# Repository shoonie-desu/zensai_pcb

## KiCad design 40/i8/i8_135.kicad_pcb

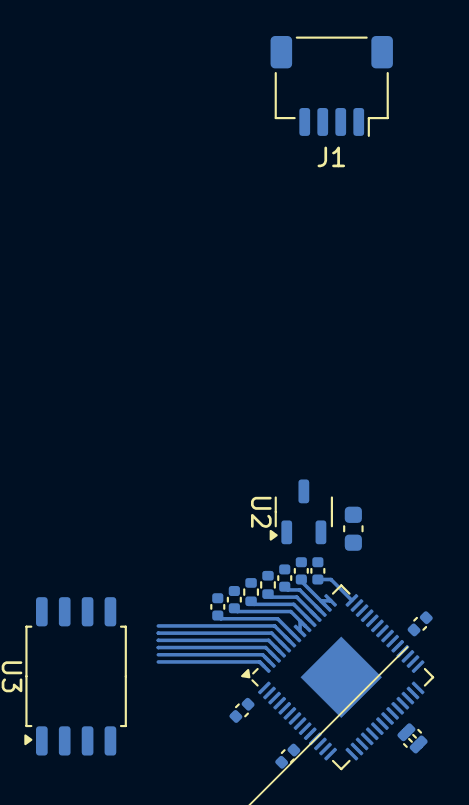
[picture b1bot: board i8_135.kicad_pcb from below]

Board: 2 copper layers, 17 parts (17 on the bottom side), 14 nets.

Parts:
C1, C5: 1u; C_0402_1005Metric
C2, C3, C6, C7, C8, C9, C10, C11: 100n; C_0402_1005Metric
C4: 10u; C_0603_1608Metric
J1: ZX-SH1.0-4PWT; JST_SH_SM04B-SRSS-TB_1x04-1MP_P1.00mm_Horizontal
R1, R2: 27; R_0402_1005Metric
U1: RP2040; QFN-56-1EP_7x7mm_P0.4mm_EP3.2x3.2mm
U2: XC6206P332MR-G; SOT-23-3
U3: W25Q128JVS; SOIC-8_5.3x5.3mm_P1.27mm

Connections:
+1V1: C1.1, C2.1, C3.1, U1.23 (DVDD), U1.45 (VREG_VOUT), U1.50 (DVDD)
+3V3: C4.1, C5.1, C6.1, C7.1, C8.1, C9.1, C10.1, C11.1, U1.1 (IOVDD), U1.10 (IOVDD), U1.22 (IOVDD), U1.33 (IOVDD), U1.42 (IOVDD), U1.43 (ADC_AVDD), U1.44 (VREG_IN), U1.48 (USB_VDD), U1.49 (IOVDD), U2.2 (VO), U3.8 (VCC)
+5V: J1.1, U2.3 (VI)
D+: J1.3, R1.1
D-: J1.2, R2.2
GND: C1.2, C2.2, C3.2, C4.2, C5.2, C6.2, C7.2, C8.2, C9.2, C10.2, C11.2, J1.4, U1.19 (TESTEN), U1.57 (GND), U2.1 (GND), U3.4 (GND)
unnamed: R2.1, U1.46 (USB_DM)
unnamed: R1.2, U1.47 (USB_DP)
Q_CLK: U1.52 (QSPI_SCLK), U3.6 (CLK)
Q_IO0: U1.53 (QSPI_SD0), U3.5 (DI/IO_{0})
Q_IO1: U1.55 (QSPI_SD1), U3.2 (DO/IO_{1})
Q_IO2: U1.54 (QSPI_SD2), U3.3 (~WP/IO_{2})
Q_IO3: U1.51 (QSPI_SD3), U3.7 (~HOLD/~RESET/IO_{3})
Q_SEL: U1.56 (QSPI_SS), U3.1 (~CS)

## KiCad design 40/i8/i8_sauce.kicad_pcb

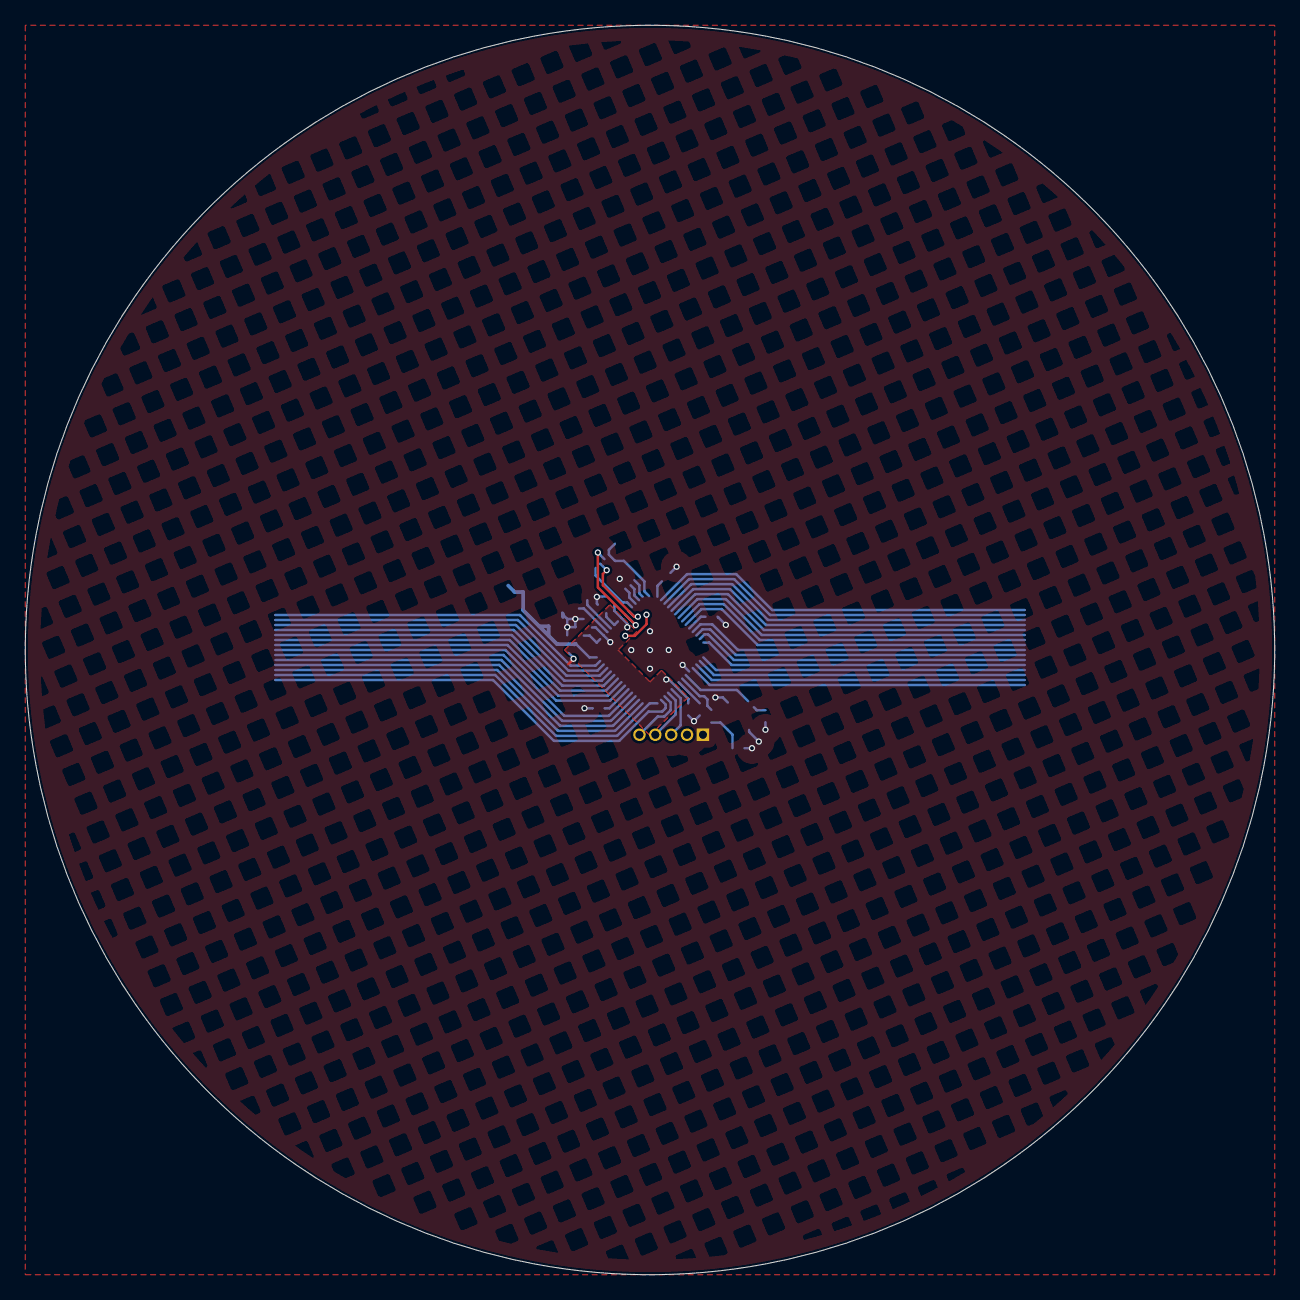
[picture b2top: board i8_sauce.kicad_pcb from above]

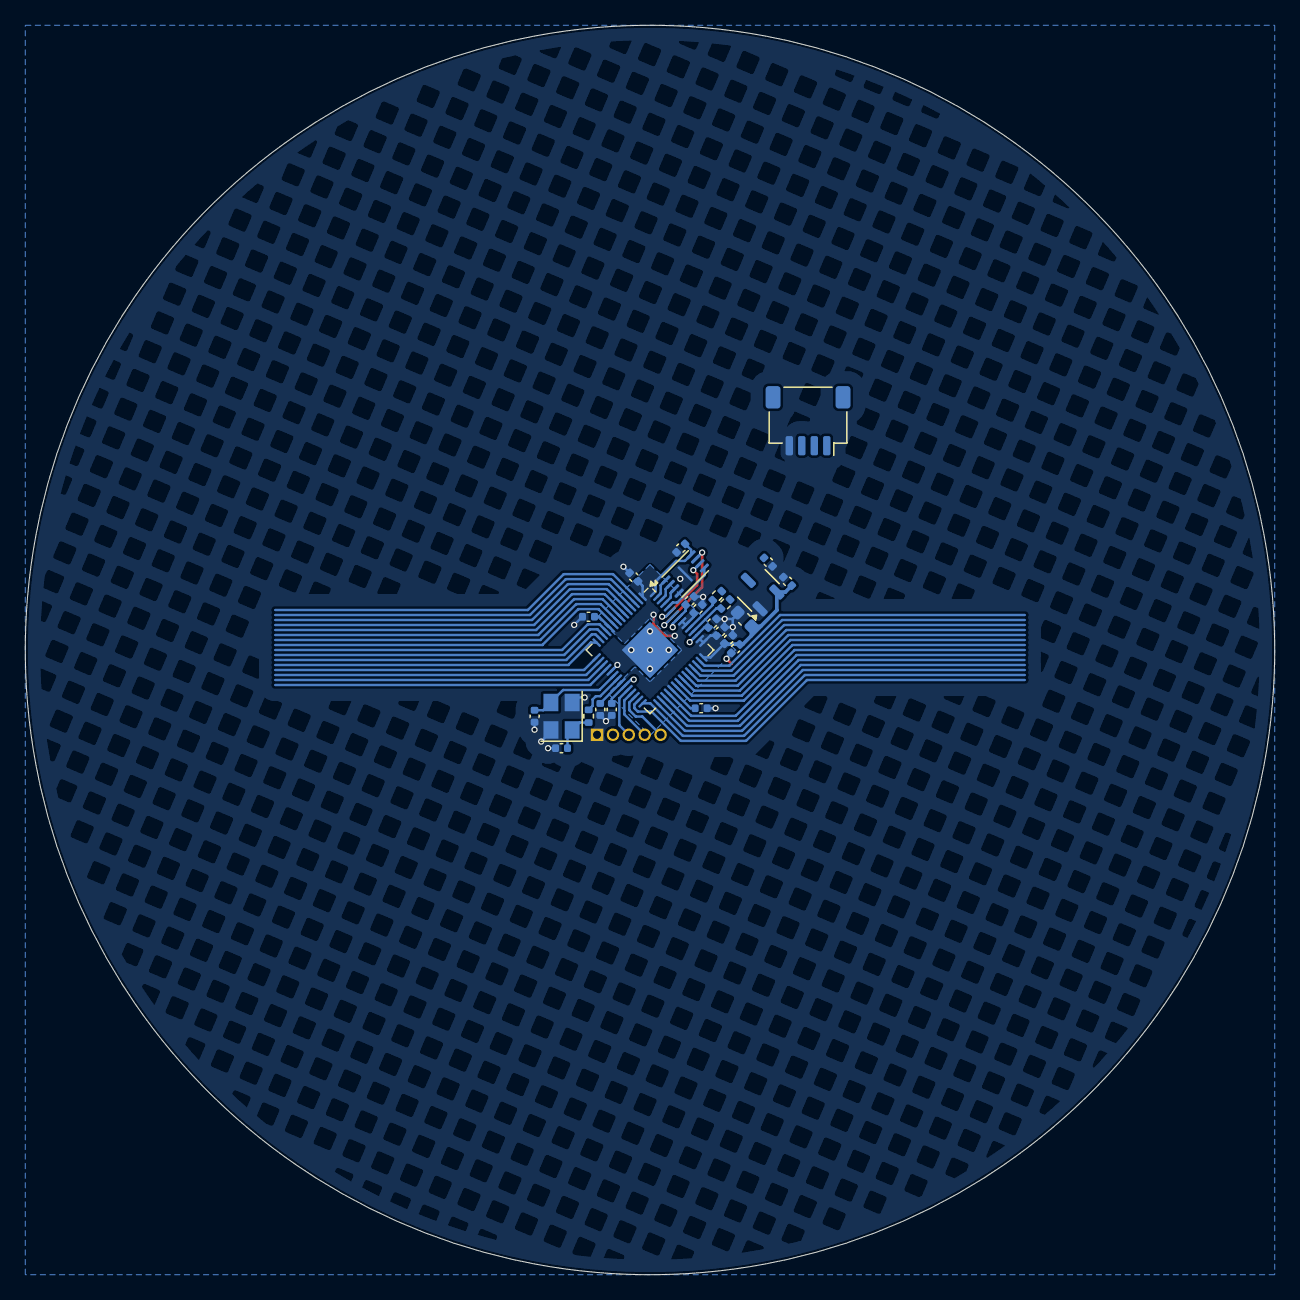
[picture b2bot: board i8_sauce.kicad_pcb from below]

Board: 2 copper layers, 100.0 x 100.0 mm, 26 parts (25 on the bottom side), 20 nets.

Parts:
C1, C5, C13, C14, C15: 1u; C_0402_1005Metric
C2, C3, C6, C7, C8, C9, C10, C11, C12: 100n; C_0402_1005Metric
C4: 10u; C_0603_1608Metric
C16, C17: 22p; C_0402_1005Metric
J1: ZX-SH1.0-4PWT; JST_SH_SM04B-SRSS-TB_1x04-1MP_P1.00mm_Horizontal
J2: Conn_DEBUG; PinHeader_1x05_P1.27mm_Vertical
R1, R2: 27; R_0402_1005Metric
R4: 1k; R_0402_1005Metric
U1: XC6206P332MR-G; SOT-23-3
U2: RP2040; QFN-56-1EP_7x7mm_P0.4mm_EP3.2x3.2mm
U3: W25Q16JVUXIQ; Winbond_USON-8-1EP_3x2mm_P0.5mm_EP0.2x1.6mm
Y1: Crystal_GND24; Crystal_SMD_3225-4Pin_3.2x2.5mm

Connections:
+1V1: C1.1, C2.1, C3.1, U2.23 (DVDD), U2.45 (VREG_VOUT), U2.50 (DVDD)
+3V3: C4.1, C5.1, C6.1, C7.1, C8.1, C9.1, C10.1, C11.1, C12.1, C14.1, C15.2, J2.2, U1.2 (VO), U2.1 (IOVDD), U2.10 (IOVDD), U2.22 (IOVDD), U2.33 (IOVDD), U2.42 (IOVDD), U2.43 (ADC_AVDD), U2.44 (VREG_IN), U2.48 (USB_VDD), U2.49 (IOVDD), U3.8 (VCC)
+5V: C13.1, J1.1, U1.3 (VI)
D+: J1.3, R1.1
D-: J1.2, R2.2
GND: C1.2, C2.2, C3.2, C4.2, C5.2, C6.2, C7.2, C8.2, C9.2, C10.2, C11.2, C12.2, C13.2, C14.2, C15.1, C16.1, C17.1, J1.4, J2.1, U1.1 (GND), U2.19 (TESTEN), U2.57 (GND), U3.4 (GND), U3.9 (EP), Y1.2, Y1.4
unnamed: C17.2, R4.2, Y1.1
unnamed: R2.1, U2.46 (USB_DM)
unnamed: R1.2, U2.47 (USB_DP)
Q_CLK: U2.52 (QSPI_SCLK), U3.6 (CLK)
Q_IO0: U2.53 (QSPI_SD0), U3.5 (DI/IO_{0})
Q_IO1: U2.55 (QSPI_SD1), U3.2 (DO/IO_{1})
Q_IO2: U2.54 (QSPI_SD2), U3.3 (~WP/IO_{2})
Q_IO3: U2.51 (QSPI_SD3), U3.7 (~HOLD/~RESET/IO_{3})
Q_SEL: U2.56 (QSPI_SS), U3.1 (~CS)
RST: J2.5, U2.26 (RUN)
SWC: J2.3, U2.24 (SWCLK)
SWD: J2.4, U2.25 (SWD)
XIN: C16.2, U2.20 (XIN), Y1.3
XOUT: R4.1, U2.21 (XOUT)

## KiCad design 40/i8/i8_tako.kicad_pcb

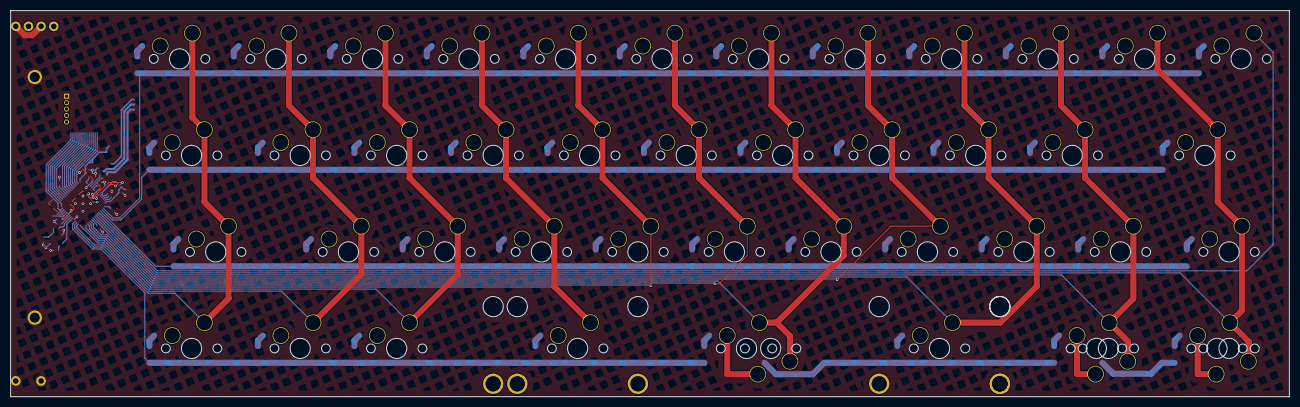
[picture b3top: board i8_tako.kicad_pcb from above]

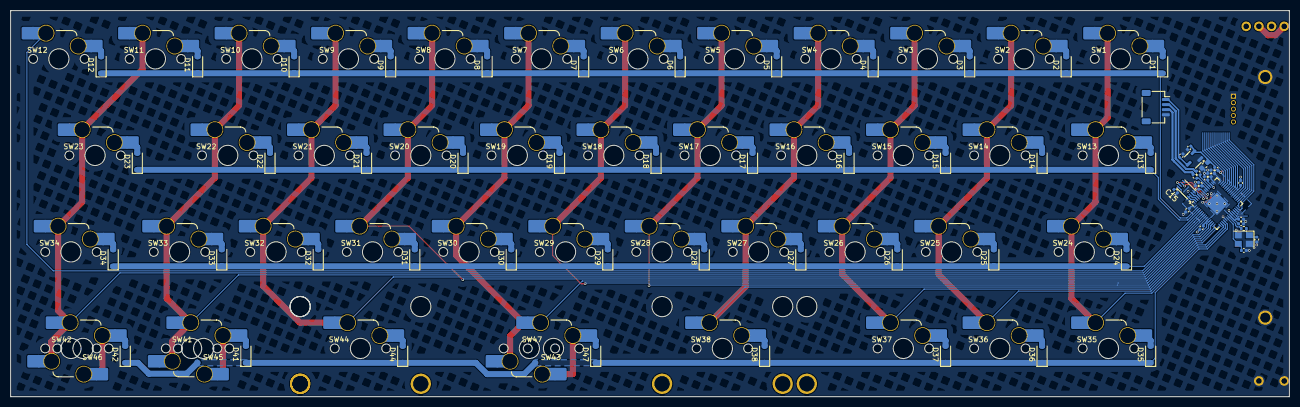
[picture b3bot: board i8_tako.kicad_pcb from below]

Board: 2 copper layers, 252.4 x 76.2 mm, 117 parts (115 on the bottom side), 79 nets.

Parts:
C1, C5, C13, C14, C15: 1u; C_0402_1005Metric
C2, C3, C6, C7, C8, C9, C10, C11, C12: 100n; C_0402_1005Metric
C4: 10u; C_0603_1608Metric
C16, C17: 22p; C_0402_1005Metric
D1, D2, D3, D4, D5, D6, D7, D8, D9, D10, D11, D12, D13, D14, D15, D16, D17, D18, D19, D20, D21, D22, D23, D24, D25, D26, D27, D28, D29, D30, D31, D32, D33, D34, D35, D36, D37, D38, D41, D42, D44, D47: 1N4148W; D_SOD-123
J1: ZX-SH1.0-4PWT; JST_SH_SM04B-SRSS-TB_1x04-1MP_P1.00mm_Horizontal
J2: Conn_DEBUG; PinHeader_1x05_P1.27mm_Vertical
R1, R2: 27; R_0402_1005Metric
R4: 1k; R_0402_1005Metric
RV1: RS6011YA600M
S38, S44: MX_S; STAB_MX_P_2u
S47: MX_S; STAB_MX_P_6.25u
SW1, SW2, SW3, SW4, SW5, SW6, SW7, SW8, SW9, SW10, SW11, SW12, SW13, SW14, SW15, SW16, SW17, SW18, SW19, SW20, SW21, SW22, SW23, SW24, SW25, SW26, SW27, SW28, SW29, SW30, SW31, SW32, SW33, SW34, SW35, SW36, SW37, SW38, SW41, SW42, SW43, SW44, SW45, SW46, SW47: MX_SW; SW_MX_HS_S_CPG151101S11_1u
U1: XC6206P332MR-G; SOT-23-3
U2: RP2040; QFN-56-1EP_7x7mm_P0.4mm_EP3.2x3.2mm
U3: W25Q16JVUXIQ; Winbond_USON-8-1EP_3x2mm_P0.5mm_EP0.2x1.6mm
Y1: Crystal_GND24; Crystal_SMD_3225-4Pin_3.2x2.5mm

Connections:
+1V1: C1.1, C2.1, C3.1, U2.23 (DVDD), U2.45 (VREG_VOUT), U2.50 (DVDD)
+3V3: C4.1, C5.1, C6.1, C7.1, C8.1, C9.1, C10.1, C11.1, C12.1, C14.1, C15.2, J2.2, RV1.1, RV1.4, U1.2 (VO), U2.1 (IOVDD), U2.10 (IOVDD), U2.22 (IOVDD), U2.33 (IOVDD), U2.42 (IOVDD), U2.43 (ADC_AVDD), U2.44 (VREG_IN), U2.48 (USB_VDD), U2.49 (IOVDD), U3.8 (VCC)
+5V: C13.1, J1.1, U1.3 (VI)
COL0: SW1.2, SW13.2, SW24.2, SW35.2, U2.17 (GPIO14)
COL1: SW2.2, SW14.2, SW25.2, SW36.2, U2.16 (GPIO13)
COL2: SW3.2, SW15.2, SW26.2, SW37.2, U2.15 (GPIO12)
COL3: SW4.2, SW16.2, SW27.2, SW38.2, U2.14 (GPIO11)
COL4: SW5.2, SW17.2, SW28.2, U2.13 (GPIO10)
COL5: SW6.2, SW18.2, SW29.2, U2.12 (GPIO9)
COL6: SW7.2, SW19.2, SW30.2, SW43.2, SW47.2, U2.11 (GPIO8)
COL7: SW8.2, SW20.2, SW31.2, U2.9 (GPIO7)
COL8: SW9.2, SW21.2, SW32.2, SW44.2, U2.8 (GPIO6)
COL9: SW10.2, SW22.2, SW33.2, SW41.2, SW45.2, U2.7 (GPIO5)
COL10: SW11.2, SW23.2, SW34.2, SW42.2, SW46.2, U2.6 (GPIO4)
COL11: SW12.2, U2.5 (GPIO3)
D+: J1.3, R1.1
D-: J1.2, R2.2
GND: C1.2, C2.2, C3.2, C4.2, C5.2, C6.2, C7.2, C8.2, C9.2, C10.2, C11.2, C12.2, C13.2, C14.2, C15.1, C16.1, C17.1, J1.4, J2.1, RV1.3, RV1.6, RV1.MP (MountPin), U1.1 (GND), U2.19 (TESTEN), U2.57 (GND), U3.4 (GND), U3.9 (EP), Y1.2, Y1.4
GPIO0: D1.1 (K), D2.1 (K), D3.1 (K), D4.1 (K), D5.1 (K), D6.1 (K), D7.1 (K), D8.1 (K), D9.1 (K), D10.1 (K), D11.1 (K), D12.1 (K), U2.2 (GPIO0)
GPIO1: D13.1 (K), D14.1 (K), D15.1 (K), D16.1 (K), D17.1 (K), D18.1 (K), D19.1 (K), D20.1 (K), D21.1 (K), D22.1 (K), D23.1 (K), U2.3 (GPIO1)
GPIO2: D24.1 (K), D25.1 (K), D26.1 (K), D27.1 (K), D28.1 (K), D29.1 (K), D30.1 (K), D31.1 (K), D32.1 (K), D33.1 (K), D34.1 (K), U2.4 (GPIO2)
GPIO15: D35.1 (K), D36.1 (K), D37.1 (K), D38.1 (K), D41.1 (K), D42.1 (K), D44.1 (K), D47.1 (K), U2.18 (GPIO15)
GPIO26_ADC0: RV1.2, U2.38 (GPIO26_ADC0)
unnamed: C17.2, R4.2, Y1.1
unnamed: D1.2 (A), SW1.1
unnamed: D2.2 (A), SW2.1
unnamed: D3.2 (A), SW3.1
unnamed: D4.2 (A), SW4.1
unnamed: D5.2 (A), SW5.1
unnamed: D6.2 (A), SW6.1
unnamed: D7.2 (A), SW7.1
unnamed: D8.2 (A), SW8.1
unnamed: D9.2 (A), SW9.1
unnamed: D10.2 (A), SW10.1
unnamed: D11.2 (A), SW11.1
unnamed: D12.2 (A), SW12.1
unnamed: D13.2 (A), SW13.1
unnamed: D14.2 (A), SW14.1
unnamed: D15.2 (A), SW15.1
unnamed: D16.2 (A), SW16.1
unnamed: D17.2 (A), SW17.1
unnamed: D18.2 (A), SW18.1
unnamed: D19.2 (A), SW19.1
unnamed: D20.2 (A), SW20.1
unnamed: D21.2 (A), SW21.1
unnamed: D22.2 (A), SW22.1
unnamed: D23.2 (A), SW23.1
unnamed: D24.2 (A), SW24.1
unnamed: D25.2 (A), SW25.1
unnamed: D26.2 (A), SW26.1
unnamed: D27.2 (A), SW27.1
unnamed: D28.2 (A), SW28.1
unnamed: D29.2 (A), SW29.1
unnamed: D30.2 (A), SW30.1
unnamed: D31.2 (A), SW31.1
unnamed: D32.2 (A), SW32.1
unnamed: D33.2 (A), SW33.1
unnamed: D34.2 (A), SW34.1
unnamed: D35.2 (A), SW35.1
unnamed: D36.2 (A), SW36.1
unnamed: D37.2 (A), SW37.1
unnamed: D38.2 (A), SW38.1
unnamed: D47.2 (A), SW43.1, SW47.1
unnamed: D44.2 (A), SW44.1
unnamed: D41.2 (A), SW41.1, SW45.1
unnamed: D42.2 (A), SW42.1, SW46.1
unnamed: R2.1, U2.46 (USB_DM)
unnamed: R1.2, U2.47 (USB_DP)
Q_CLK: U2.52 (QSPI_SCLK), U3.6 (CLK)
Q_IO0: U2.53 (QSPI_SD0), U3.5 (DI/IO_{0})
Q_IO1: U2.55 (QSPI_SD1), U3.2 (DO/IO_{1})
Q_IO2: U2.54 (QSPI_SD2), U3.3 (~WP/IO_{2})
Q_IO3: U2.51 (QSPI_SD3), U3.7 (~HOLD/~RESET/IO_{3})
Q_SEL: U2.56 (QSPI_SS), U3.1 (~CS)
RST: J2.5, U2.26 (RUN)
SWC: J2.3, U2.24 (SWCLK)
SWD: J2.4, U2.25 (SWD)
XIN: C16.2, U2.20 (XIN), Y1.3
XOUT: R4.1, U2.21 (XOUT)

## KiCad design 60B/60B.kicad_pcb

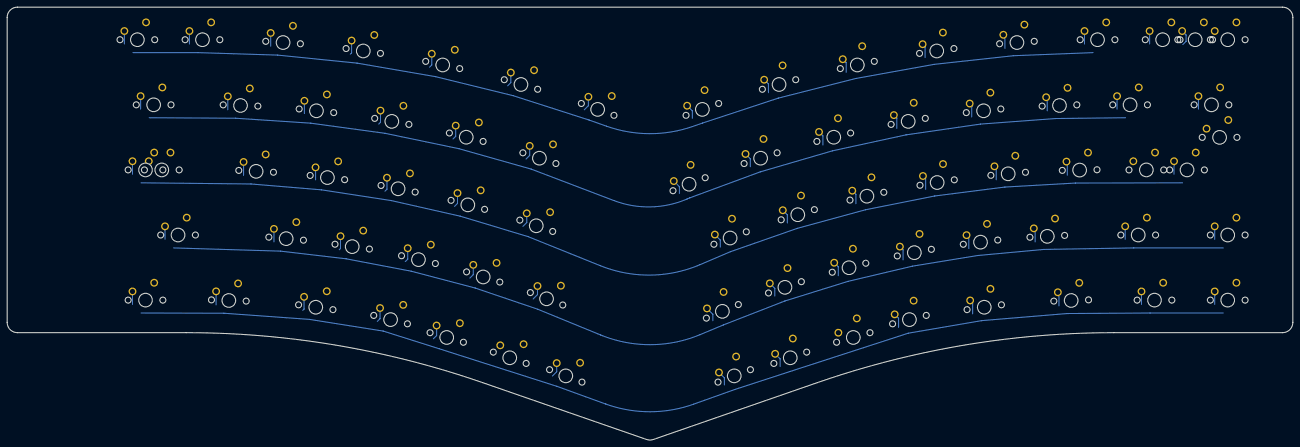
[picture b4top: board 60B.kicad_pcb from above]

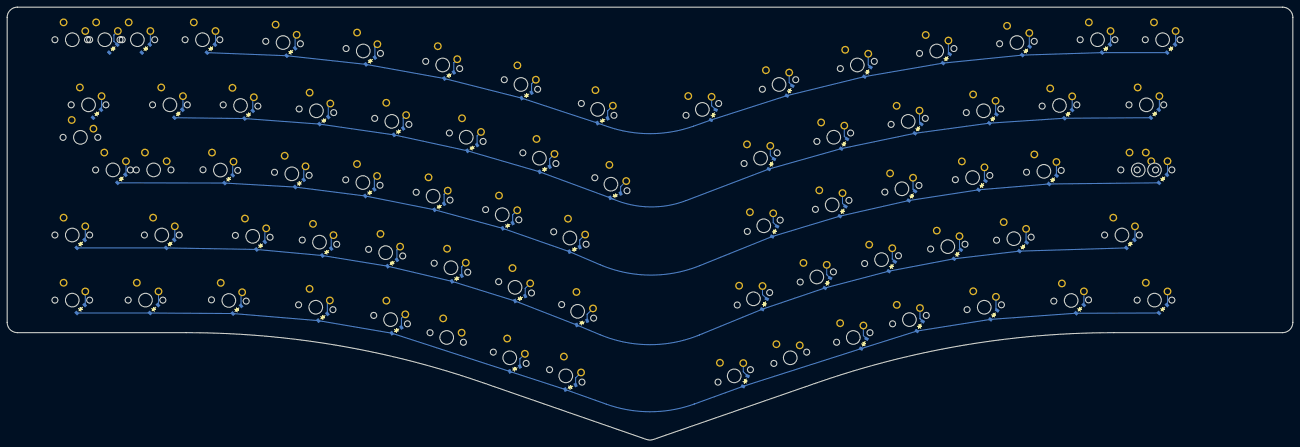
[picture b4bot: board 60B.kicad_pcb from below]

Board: 2 copper layers, 376.2 x 126.7 mm, 144 parts (69 on the bottom side), 74 nets.

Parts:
D1, D2, D3, D4, D5, D6, D7, D8, D9, D10, D11, D12, D13, D14, D16, D17, D18, D19, D20, D21, D22, D23, D24, D25, D26, D27, D28, D29, D30, D32, D33, D34, D35, D36, D37, D38, D39, D40, D41, D42, D43, D45, D47, D48, D49, D50, D51, D52, D53, D54, D55, D56, D57, D58, D59, D60, D61, D62, D63, D64, D65, D67, D68, D69, D71, D72, D73, D74, D75: D_Small; D_SOD-123_CLEAN
MX1, MX2, MX3, MX4, MX5, MX6, MX7, MX8, MX9, MX10, MX11, MX12, MX13, MX14, MX15, MX16, MX17, MX18, MX19, MX20, MX21, MX22, MX23, MX24, MX25, MX26, MX27, MX28, MX29, MX30, MX31, MX32, MX33, MX34, MX35, MX36, MX37, MX38, MX39, MX40, MX41, MX42, MX43, MX44, MX45, MX46, MX47, MX48, MX49, MX50, MX51, MX52, MX53, MX54, MX55, MX56, MX57, MX58, MX59, MX60, MX61, MX62, MX63, MX64, MX65, MX66, MX67, MX68, MX69, MX70, MX71, MX72, MX73, MX74, MX75: MX_SW_solder; SW_MX_1u

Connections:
unnamed: D1.2 (A), MX1.1
unnamed: D1.1 (K), D2.1 (K), D3.1 (K), D4.1 (K), D5.1 (K), D6.1 (K), D7.1 (K), D8.1 (K), D9.1 (K), D10.1 (K), D11.1 (K), D12.1 (K), D13.1 (K), D14.1 (K)
unnamed: D2.2 (A), MX2.1
unnamed: D3.2 (A), MX3.1
unnamed: D4.2 (A), MX4.1
unnamed: D5.2 (A), MX5.1
unnamed: D6.2 (A), MX6.1
unnamed: D7.2 (A), MX7.1
unnamed: D8.2 (A), MX8.1
unnamed: D9.2 (A), MX9.1
unnamed: D10.2 (A), MX10.1
unnamed: D11.2 (A), MX11.1
unnamed: D12.2 (A), MX12.1
unnamed: D13.2 (A), MX13.1
unnamed: D14.2 (A), MX14.1
unnamed: D16.2 (A), MX16.1
unnamed: D16.1 (K), D17.1 (K), D18.1 (K), D19.1 (K), D20.1 (K), D21.1 (K), D22.1 (K), D23.1 (K), D24.1 (K), D25.1 (K), D26.1 (K), D27.1 (K), D28.1 (K), D29.1 (K)
unnamed: D17.2 (A), MX17.1
unnamed: D18.2 (A), MX18.1
unnamed: D19.2 (A), MX19.1
unnamed: D20.2 (A), MX20.1
unnamed: D21.2 (A), MX21.1
unnamed: D22.2 (A), MX22.1
unnamed: D23.2 (A), MX23.1
unnamed: D24.2 (A), MX24.1
unnamed: D25.2 (A), MX25.1
unnamed: D26.2 (A), MX26.1
unnamed: D27.2 (A), MX27.1
unnamed: D28.2 (A), MX28.1
unnamed: D29.2 (A), MX29.1
unnamed: D30.2 (A), MX30.1
unnamed: D30.1 (K), D32.1 (K), D33.1 (K), D34.1 (K), D35.1 (K), D36.1 (K), D37.1 (K), D38.1 (K), D39.1 (K), D40.1 (K), D41.1 (K), D42.1 (K), D43.1 (K), D45.1 (K)
unnamed: D32.2 (A), MX32.1
unnamed: D33.2 (A), MX33.1
unnamed: D34.2 (A), MX34.1
unnamed: D35.2 (A), MX35.1
unnamed: D36.2 (A), MX36.1
unnamed: D37.2 (A), MX37.1
unnamed: D38.2 (A), MX38.1
unnamed: D39.2 (A), MX39.1
unnamed: D40.2 (A), MX40.1
unnamed: D41.2 (A), MX41.1
unnamed: D42.2 (A), MX42.1
unnamed: D43.2 (A), MX43.1
unnamed: D45.2 (A), MX45.1
unnamed: D47.2 (A), MX47.1
unnamed: D47.1 (K), D48.1 (K), D49.1 (K), D50.1 (K), D51.1 (K), D52.1 (K), D53.1 (K), D54.1 (K), D55.1 (K), D56.1 (K), D57.1 (K), D58.1 (K), D59.1 (K), D60.1 (K)
unnamed: D48.2 (A), MX48.1
unnamed: D49.2 (A), MX49.1
unnamed: D50.2 (A), MX50.1
unnamed: D51.2 (A), MX51.1
unnamed: D52.2 (A), MX52.1
unnamed: D53.2 (A), MX53.1
unnamed: D54.2 (A), MX54.1
unnamed: D55.2 (A), MX55.1
unnamed: D56.2 (A), MX56.1
unnamed: D57.2 (A), MX57.1
unnamed: D58.2 (A), MX58.1
unnamed: D59.2 (A), MX59.1
unnamed: D60.2 (A), MX60.1
unnamed: D61.2 (A), MX61.1
unnamed: D61.1 (K), D62.1 (K), D63.1 (K), D64.1 (K), D65.1 (K), D67.1 (K), D68.1 (K), D69.1 (K), D71.1 (K), D72.1 (K), D73.1 (K), D74.1 (K), D75.1 (K)
unnamed: D62.2 (A), MX62.1
unnamed: D63.2 (A), MX63.1
unnamed: D64.2 (A), MX64.1
unnamed: D65.2 (A), MX65.1
unnamed: D67.2 (A), MX67.1
unnamed: D68.2 (A), MX68.1
unnamed: D69.2 (A), MX69.1
unnamed: D71.2 (A), MX71.1
unnamed: D72.2 (A), MX72.1
unnamed: D73.2 (A), MX73.1
unnamed: D74.2 (A), MX74.1
unnamed: D75.2 (A), MX75.1

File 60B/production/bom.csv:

Designator,Footprint,Quantity,Value,LCSC Part #
"D1, D10, D11, D12, D13, D14, D16, D17, D18, D19, D2, D20, D21, D22, D23, D24, D25, D26, D27, D28, D29, D3, D30, D32, D33, D34, D35, D36, D37, D38, D39, D4, D40, D41, D42, D43, D45, D47, D48, D49, D5, D50, D51, D52, D53, D54, D55, D56, D57, D58, D59, D6, D60, D61, D62, D63, D64, D65, D67, D68, D69, D7, D71, D72, D73, D74, D75, D8, D9",D_SOD-123_CLEAN,69,D_Small,
"MX1, MX10, MX11, MX12, MX13, MX14, MX15, MX16, MX17, MX18, MX19, MX2, MX20, MX21, MX22, MX23, MX24, MX25, MX26, MX27, MX28, MX29, MX3, MX30, MX31, MX32, MX33, MX34, MX35, MX36, MX37, MX38, MX39, MX4, MX40, MX41, MX42, MX43, MX44, MX45, MX46, MX47, MX48, MX49, MX5, MX50, MX51, MX52, MX53, MX54, MX55, MX56, MX57, MX58, MX59, MX6, MX60, MX61, MX62, MX63, MX64, MX65, MX66, MX67, MX68, MX69, MX7, MX70, MX71, MX72, MX73, MX74, MX75, MX8, MX9",SW_MX_1u,75,MX_SW_solder,
